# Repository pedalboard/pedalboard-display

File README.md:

# Pedalboard Display

LED ring and OLED display PCB for the [Open Pedalboard](https://github.com/pedalboard) system.

**[Documentation →](https://pedalboard.github.io/pedalboard-display/latest/)**

## Features

- 8 cascaded RGB LED rings (12 individually addressable LEDs each)
- Single serial line addressing (Stemma 3-pin JST-PH)
- 2 additional single LEDs
- 2 ports for 4-wire OLED displays (Stemma 4-pin connectors)

## Links

- [Interactive schematic & PCB viewer](https://pedalboard.github.io/pedalboard-display/latest/board/)
- [DigiKey shared list](https://www.digikey.ch/en/mylists/list/VCPAA9117V)
- Foot switch actuator: [Data Sheet](https://www.cliffuk.co.uk/products/switches/FC7125.pdf) / [3D Model](https://github.com/pedalboard/pedalboard-case/blob/main/generated/actuator.stl)

## License

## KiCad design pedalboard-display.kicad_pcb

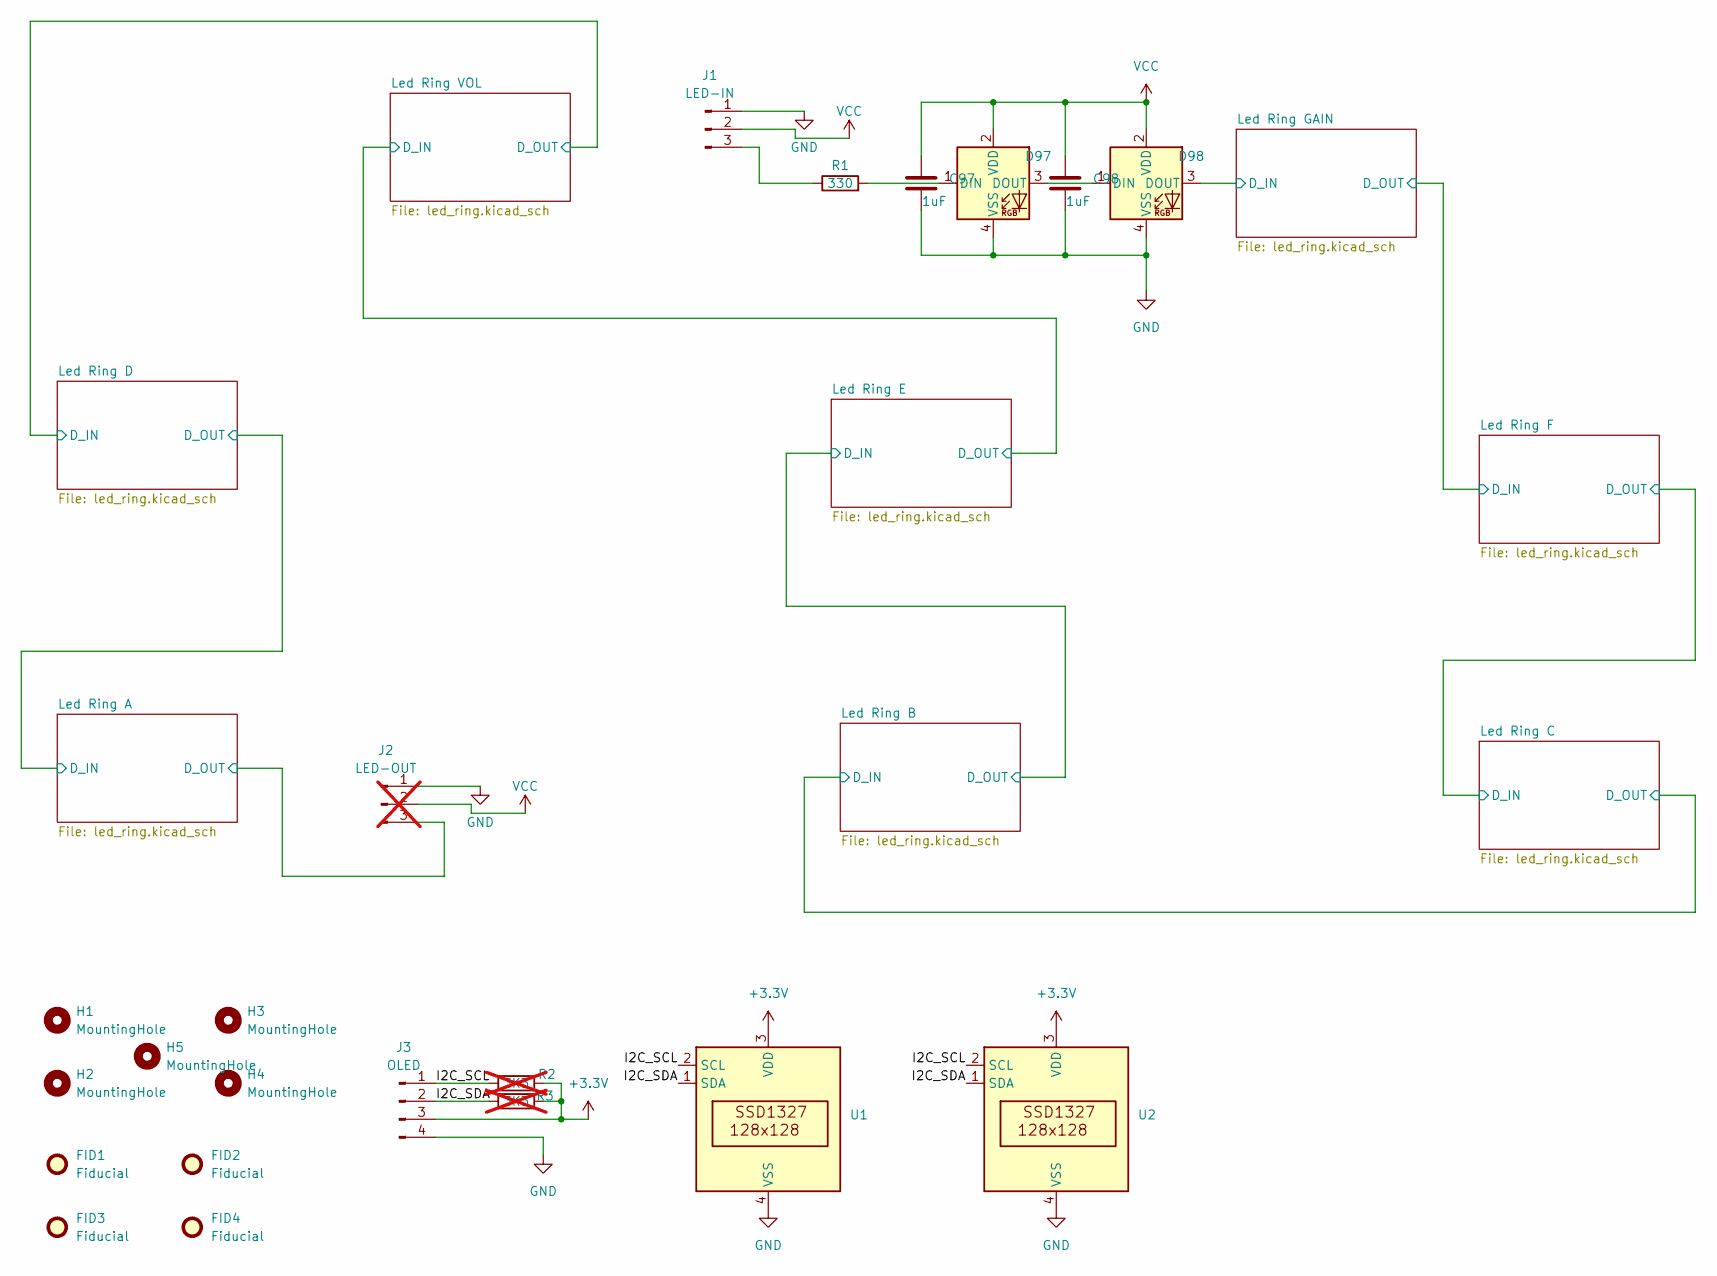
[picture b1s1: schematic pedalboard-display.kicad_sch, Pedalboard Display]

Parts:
C97, C98: 1uF; C_0402_1005Metric
D97, D98: SK6812_EC15; LED_SK6812_EC15_1.5x1.5mm
FID1, FID2, FID3, FID4: Fiducial; Fiducial_0.5mm_Mask1mm
H1, H2, H3, H4, H5: MountingHole; MountingHole_2.5mm
J1: LED-IN; JST_PH_B3B-PH-SM4-TB_1x03-1MP_P2.00mm_Vertical
J2: LED-OUT; JST_PH_B3B-PH-SM4-TB_1x03-1MP_P2.00mm_Vertical; not fitted
J3: OLED; JST_PH_B4B-PH-SM4-TB_1x04-1MP_P2.00mm_Vertical
R1: 330; R_0402_1005Metric
R2, R3: 3K3; R_0805_2012Metric; not fitted
U1, U2: OLED_128x128

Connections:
+3.3V: J3.3, R2.1, R3.1, U1.3 (VDD), U2.3 (VDD)
/I2C_SCL: J3.1, R2.2, U1.2 (SCL), U2.2 (SCL)
/I2C_SDA: J3.2, R3.2, U1.1 (SDA), U2.1 (SDA)
/Led Ring A/D_OUT: J2.3; also elsewhere on the board
/Led Ring GAIN/D_IN: D98.3 (DOUT); also elsewhere on the board
GND: C97.2, C98.2, D97.4 (VSS), D98.4 (VSS), J1.1, J2.1, J3.4, U1.4 (VSS), U2.4 (VSS); also elsewhere on the board
unnamed: D97.1 (DIN), R1.2
unnamed: D97.3 (DOUT), D98.1 (DIN)
unnamed: J1.3, R1.1
VCC: C97.1, C98.1, D97.2 (VDD), D98.2 (VDD), J1.2, J2.2; also elsewhere on the board

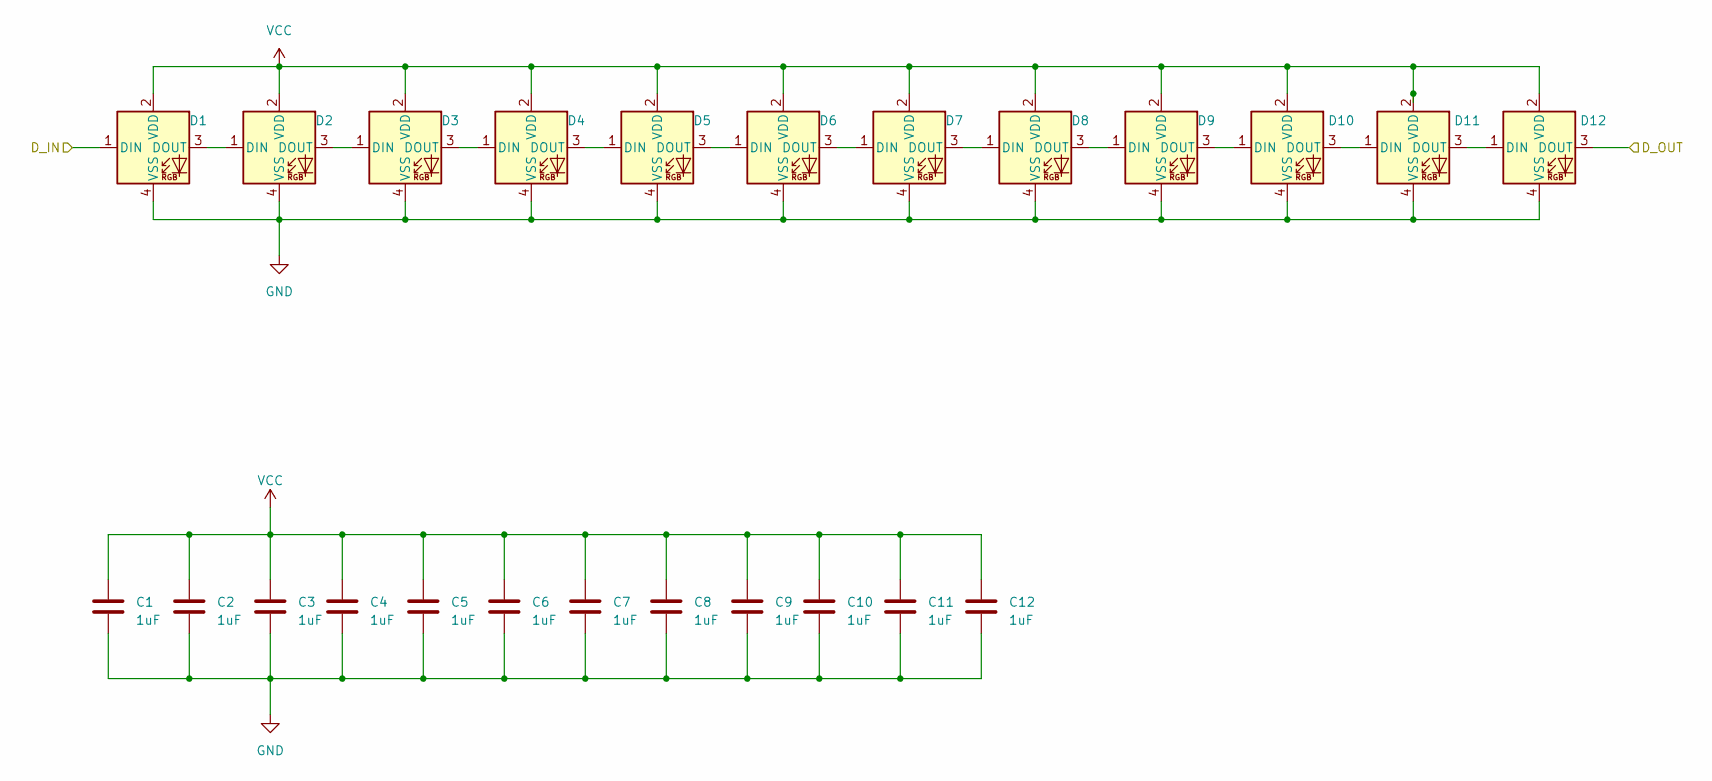
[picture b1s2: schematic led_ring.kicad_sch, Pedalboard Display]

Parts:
C1, C2, C3, C4, C5, C6, C7, C8, C9, C10, C11, C12: 1uF; C_0402_1005Metric
D1, D2, D3, D4, D5, D6, D7, D8, D9, D10, D11, D12: SK6812_EC15; LED_SK6812_EC15_1.5x1.5mm

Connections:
/Led Ring F/D_IN: D12.3 (DOUT); also elsewhere on the board
/Led Ring GAIN/D_IN: D1.1 (DIN); also elsewhere on the board
GND: C1.2, C2.2, C3.2, C4.2, C5.2, C6.2, C7.2, C8.2, C9.2, C10.2, C11.2, C12.2, D1.4 (VSS), D2.4 (VSS), D3.4 (VSS), D4.4 (VSS), D5.4 (VSS), D6.4 (VSS), D7.4 (VSS), D8.4 (VSS), D9.4 (VSS), D10.4 (VSS), D11.4 (VSS), D12.4 (VSS); also elsewhere on the board
unnamed: D1.3 (DOUT), D2.1 (DIN)
unnamed: D2.3 (DOUT), D3.1 (DIN)
unnamed: D3.3 (DOUT), D4.1 (DIN)
unnamed: D4.3 (DOUT), D5.1 (DIN)
unnamed: D5.3 (DOUT), D6.1 (DIN)
unnamed: D6.3 (DOUT), D7.1 (DIN)
unnamed: D7.3 (DOUT), D8.1 (DIN)
unnamed: D8.3 (DOUT), D9.1 (DIN)
unnamed: D9.3 (DOUT), D10.1 (DIN)
unnamed: D10.3 (DOUT), D11.1 (DIN)
unnamed: D11.3 (DOUT), D12.1 (DIN)
VCC: C1.1, C2.1, C3.1, C4.1, C5.1, C6.1, C7.1, C8.1, C9.1, C10.1, C11.1, C12.1, D1.2 (VDD), D2.2 (VDD), D3.2 (VDD), D4.2 (VDD), D5.2 (VDD), D6.2 (VDD), D7.2 (VDD), D8.2 (VDD), D9.2 (VDD), D10.2 (VDD), D11.2 (VDD), D12.2 (VDD); also elsewhere on the board

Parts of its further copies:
C13, C14, C15, C16, C17, C18, C19, C20, C21, C22, C23, C24, C25, C26, C27, C28, C29, C30, C31, C32, C33, C34, C35, C36, C37, C38, C39, C40, C41, C42, C43, C44, C45, C46, C47, C48, C49, C50, C51, C52, C53, C54, C55, C56, C57, C58, C59, C60, C61, C62, C63, C64, C65, C66, C67, C68, C69, C70, C71, C72, C73, C74, C75, C76, C77, C78, C79, C80, C81, C82, C83, C84, C85, C86, C87, C88, C89, C90, C91, C92, C93, C94, C95, C96: 1uF; C_0402_1005Metric
D13, D14, D15, D16, D17, D18, D19, D20, D21, D22, D23, D24, D25, D26, D27, D28, D29, D30, D31, D32, D33, D34, D35, D36, D37, D38, D39, D40, D41, D42, D43, D44, D45, D46, D47, D48, D49, D50, D51, D52, D53, D54, D55, D56, D57, D58, D59, D60, D61, D62, D63, D64, D65, D66, D67, D68, D69, D70, D71, D72, D73, D74, D75, D76, D77, D78, D79, D80, D81, D82, D83, D84, D85, D86, D87, D88, D89, D90, D91, D92, D93, D94, D95, D96: SK6812_EC15; LED_SK6812_EC15_1.5x1.5mm

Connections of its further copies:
/Led Ring A/D_IN: D84.3 (DOUT), D85.1 (DIN)
/Led Ring A/D_OUT: D96.3 (DOUT); also elsewhere on the board
/Led Ring B/D_IN: D36.3 (DOUT), D37.1 (DIN)
/Led Ring B/D_OUT: D48.3 (DOUT), D49.1 (DIN)
/Led Ring C/D_IN: D24.3 (DOUT), D25.1 (DIN)
/Led Ring D/D_IN: D72.3 (DOUT), D73.1 (DIN)
/Led Ring E/D_OUT: D60.3 (DOUT), D61.1 (DIN)
/Led Ring F/D_IN: D13.1 (DIN); also elsewhere on the board
GND: C13.2, C14.2, C15.2, C16.2, C17.2, C18.2, C19.2, C20.2, C21.2, C22.2, C23.2, C24.2, C25.2, C26.2, C27.2, C28.2, C29.2, C30.2, C31.2, C32.2, C33.2, C34.2, C35.2, C36.2, C37.2, C38.2, C39.2, C40.2, C41.2, C42.2, C43.2, C44.2, C45.2, C46.2, C47.2, C48.2, C49.2, C50.2, C51.2, C52.2, C53.2, C54.2, C55.2, C56.2, C57.2, C58.2, C59.2, C60.2, C61.2, C62.2, C63.2, C64.2, C65.2, C66.2, C67.2, C68.2, C69.2, C70.2, C71.2, C72.2, C73.2, C74.2, C75.2, C76.2, C77.2, C78.2, C79.2, C80.2, C81.2, C82.2, C83.2, C84.2, C85.2, C86.2, C87.2, C88.2, C89.2, C90.2, C91.2, C92.2, C93.2, C94.2, C95.2, C96.2, D13.4 (VSS), D14.4 (VSS), D15.4 (VSS), D16.4 (VSS), D17.4 (VSS), D18.4 (VSS), D19.4 (VSS), D20.4 (VSS), D21.4 (VSS), D22.4 (VSS), D23.4 (VSS), D24.4 (VSS), D25.4 (VSS), D26.4 (VSS), D27.4 (VSS), D28.4 (VSS), D29.4 (VSS), D30.4 (VSS), D31.4 (VSS), D32.4 (VSS), D33.4 (VSS), D34.4 (VSS), D35.4 (VSS), D36.4 (VSS), D37.4 (VSS), D38.4 (VSS), D39.4 (VSS), D40.4 (VSS), D41.4 (VSS), D42.4 (VSS), D43.4 (VSS), D44.4 (VSS), D45.4 (VSS), D46.4 (VSS), D47.4 (VSS), D48.4 (VSS), D49.4 (VSS), D50.4 (VSS), D51.4 (VSS), D52.4 (VSS), D53.4 (VSS), D54.4 (VSS), D55.4 (VSS), D56.4 (VSS), D57.4 (VSS), D58.4 (VSS), D59.4 (VSS), D60.4 (VSS), D61.4 (VSS), D62.4 (VSS), D63.4 (VSS), D64.4 (VSS), D65.4 (VSS), D66.4 (VSS), D67.4 (VSS), D68.4 (VSS), D69.4 (VSS), D70.4 (VSS), D71.4 (VSS), D72.4 (VSS), D73.4 (VSS), D74.4 (VSS), D75.4 (VSS), D76.4 (VSS), D77.4 (VSS), D78.4 (VSS), D79.4 (VSS), D80.4 (VSS), D81.4 (VSS), D82.4 (VSS), D83.4 (VSS), D84.4 (VSS), D85.4 (VSS), D86.4 (VSS), D87.4 (VSS), D88.4 (VSS), D89.4 (VSS), D90.4 (VSS), D91.4 (VSS), D92.4 (VSS), D93.4 (VSS), D94.4 (VSS), D95.4 (VSS), D96.4 (VSS); also elsewhere on the board
unnamed: D13.3 (DOUT), D14.1 (DIN)
unnamed: D14.3 (DOUT), D15.1 (DIN)
unnamed: D15.3 (DOUT), D16.1 (DIN)
unnamed: D16.3 (DOUT), D17.1 (DIN)
unnamed: D17.3 (DOUT), D18.1 (DIN)
unnamed: D18.3 (DOUT), D19.1 (DIN)
unnamed: D19.3 (DOUT), D20.1 (DIN)
unnamed: D20.3 (DOUT), D21.1 (DIN)
unnamed: D21.3 (DOUT), D22.1 (DIN)
unnamed: D22.3 (DOUT), D23.1 (DIN)
unnamed: D23.3 (DOUT), D24.1 (DIN)
unnamed: D25.3 (DOUT), D26.1 (DIN)
unnamed: D26.3 (DOUT), D27.1 (DIN)
unnamed: D27.3 (DOUT), D28.1 (DIN)
unnamed: D28.3 (DOUT), D29.1 (DIN)
unnamed: D29.3 (DOUT), D30.1 (DIN)
unnamed: D30.3 (DOUT), D31.1 (DIN)
unnamed: D31.3 (DOUT), D32.1 (DIN)
unnamed: D32.3 (DOUT), D33.1 (DIN)
unnamed: D33.3 (DOUT), D34.1 (DIN)
unnamed: D34.3 (DOUT), D35.1 (DIN)
unnamed: D35.3 (DOUT), D36.1 (DIN)
unnamed: D37.3 (DOUT), D38.1 (DIN)
unnamed: D38.3 (DOUT), D39.1 (DIN)
unnamed: D39.3 (DOUT), D40.1 (DIN)
unnamed: D40.3 (DOUT), D41.1 (DIN)
unnamed: D41.3 (DOUT), D42.1 (DIN)
unnamed: D42.3 (DOUT), D43.1 (DIN)
unnamed: D43.3 (DOUT), D44.1 (DIN)
unnamed: D44.3 (DOUT), D45.1 (DIN)
unnamed: D45.3 (DOUT), D46.1 (DIN)
unnamed: D46.3 (DOUT), D47.1 (DIN)
unnamed: D47.3 (DOUT), D48.1 (DIN)
unnamed: D49.3 (DOUT), D50.1 (DIN)
unnamed: D50.3 (DOUT), D51.1 (DIN)
unnamed: D51.3 (DOUT), D52.1 (DIN)
unnamed: D52.3 (DOUT), D53.1 (DIN)
unnamed: D53.3 (DOUT), D54.1 (DIN)
unnamed: D54.3 (DOUT), D55.1 (DIN)
unnamed: D55.3 (DOUT), D56.1 (DIN)
unnamed: D56.3 (DOUT), D57.1 (DIN)
unnamed: D57.3 (DOUT), D58.1 (DIN)
unnamed: D58.3 (DOUT), D59.1 (DIN)
unnamed: D59.3 (DOUT), D60.1 (DIN)
unnamed: D61.3 (DOUT), D62.1 (DIN)
unnamed: D62.3 (DOUT), D63.1 (DIN)
unnamed: D63.3 (DOUT), D64.1 (DIN)
unnamed: D64.3 (DOUT), D65.1 (DIN)
unnamed: D65.3 (DOUT), D66.1 (DIN)
unnamed: D66.3 (DOUT), D67.1 (DIN)
unnamed: D67.3 (DOUT), D68.1 (DIN)
unnamed: D68.3 (DOUT), D69.1 (DIN)
unnamed: D69.3 (DOUT), D70.1 (DIN)
unnamed: D70.3 (DOUT), D71.1 (DIN)
unnamed: D71.3 (DOUT), D72.1 (DIN)
unnamed: D73.3 (DOUT), D74.1 (DIN)
unnamed: D74.3 (DOUT), D75.1 (DIN)
unnamed: D75.3 (DOUT), D76.1 (DIN)
unnamed: D76.3 (DOUT), D77.1 (DIN)
unnamed: D77.3 (DOUT), D78.1 (DIN)
unnamed: D78.3 (DOUT), D79.1 (DIN)
unnamed: D79.3 (DOUT), D80.1 (DIN)
unnamed: D80.3 (DOUT), D81.1 (DIN)
unnamed: D81.3 (DOUT), D82.1 (DIN)
unnamed: D82.3 (DOUT), D83.1 (DIN)
unnamed: D83.3 (DOUT), D84.1 (DIN)
unnamed: D85.3 (DOUT), D86.1 (DIN)
unnamed: D86.3 (DOUT), D87.1 (DIN)
unnamed: D87.3 (DOUT), D88.1 (DIN)
unnamed: D88.3 (DOUT), D89.1 (DIN)
unnamed: D89.3 (DOUT), D90.1 (DIN)
unnamed: D90.3 (DOUT), D91.1 (DIN)
unnamed: D91.3 (DOUT), D92.1 (DIN)
unnamed: D92.3 (DOUT), D93.1 (DIN)
unnamed: D93.3 (DOUT), D94.1 (DIN)
unnamed: D94.3 (DOUT), D95.1 (DIN)
unnamed: D95.3 (DOUT), D96.1 (DIN)
VCC: C13.1, C14.1, C15.1, C16.1, C17.1, C18.1, C19.1, C20.1, C21.1, C22.1, C23.1, C24.1, C25.1, C26.1, C27.1, C28.1, C29.1, C30.1, C31.1, C32.1, C33.1, C34.1, C35.1, C36.1, C37.1, C38.1, C39.1, C40.1, C41.1, C42.1, C43.1, C44.1, C45.1, C46.1, C47.1, C48.1, C49.1, C50.1, C51.1, C52.1, C53.1, C54.1, C55.1, C56.1, C57.1, C58.1, C59.1, C60.1, C61.1, C62.1, C63.1, C64.1, C65.1, C66.1, C67.1, C68.1, C69.1, C70.1, C71.1, C72.1, C73.1, C74.1, C75.1, C76.1, C77.1, C78.1, C79.1, C80.1, C81.1, C82.1, C83.1, C84.1, C85.1, C86.1, C87.1, C88.1, C89.1, C90.1, C91.1, C92.1, C93.1, C94.1, C95.1, C96.1, D13.2 (VDD), D14.2 (VDD), D15.2 (VDD), D16.2 (VDD), D17.2 (VDD), D18.2 (VDD), D19.2 (VDD), D20.2 (VDD), D21.2 (VDD), D22.2 (VDD), D23.2 (VDD), D24.2 (VDD), D25.2 (VDD), D26.2 (VDD), D27.2 (VDD), D28.2 (VDD), D29.2 (VDD), D30.2 (VDD), D31.2 (VDD), D32.2 (VDD), D33.2 (VDD), D34.2 (VDD), D35.2 (VDD), D36.2 (VDD), D37.2 (VDD), D38.2 (VDD), D39.2 (VDD), D40.2 (VDD), D41.2 (VDD), D42.2 (VDD), D43.2 (VDD), D44.2 (VDD), D45.2 (VDD), D46.2 (VDD), D47.2 (VDD), D48.2 (VDD), D49.2 (VDD), D50.2 (VDD), D51.2 (VDD), D52.2 (VDD), D53.2 (VDD), D54.2 (VDD), D55.2 (VDD), D56.2 (VDD), D57.2 (VDD), D58.2 (VDD), D59.2 (VDD), D60.2 (VDD), D61.2 (VDD), D62.2 (VDD), D63.2 (VDD), D64.2 (VDD), D65.2 (VDD), D66.2 (VDD), D67.2 (VDD), D68.2 (VDD), D69.2 (VDD), D70.2 (VDD), D71.2 (VDD), D72.2 (VDD), D73.2 (VDD), D74.2 (VDD), D75.2 (VDD), D76.2 (VDD), D77.2 (VDD), D78.2 (VDD), D79.2 (VDD), D80.2 (VDD), D81.2 (VDD), D82.2 (VDD), D83.2 (VDD), D84.2 (VDD), D85.2 (VDD), D86.2 (VDD), D87.2 (VDD), D88.2 (VDD), D89.2 (VDD), D90.2 (VDD), D91.2 (VDD), D92.2 (VDD), D93.2 (VDD), D94.2 (VDD), D95.2 (VDD), D96.2 (VDD); also elsewhere on the board

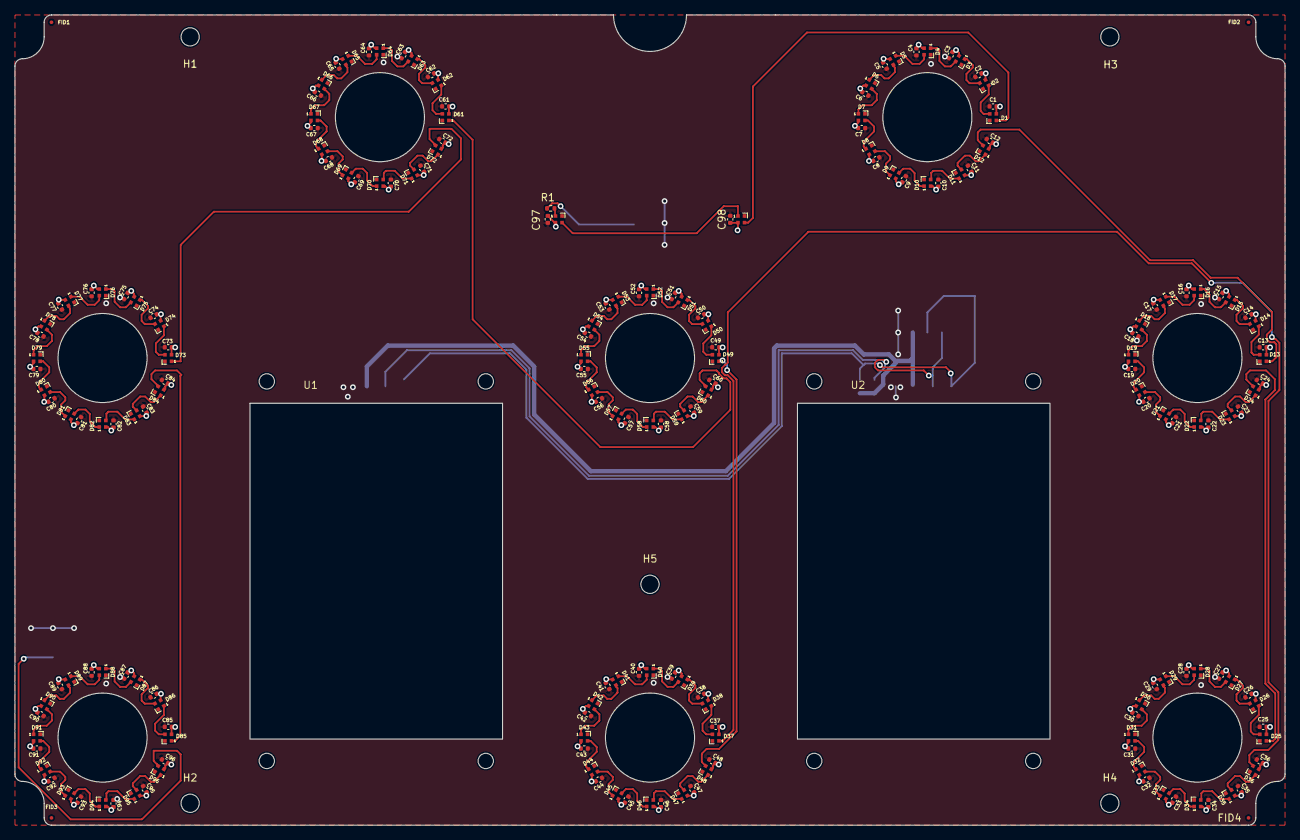
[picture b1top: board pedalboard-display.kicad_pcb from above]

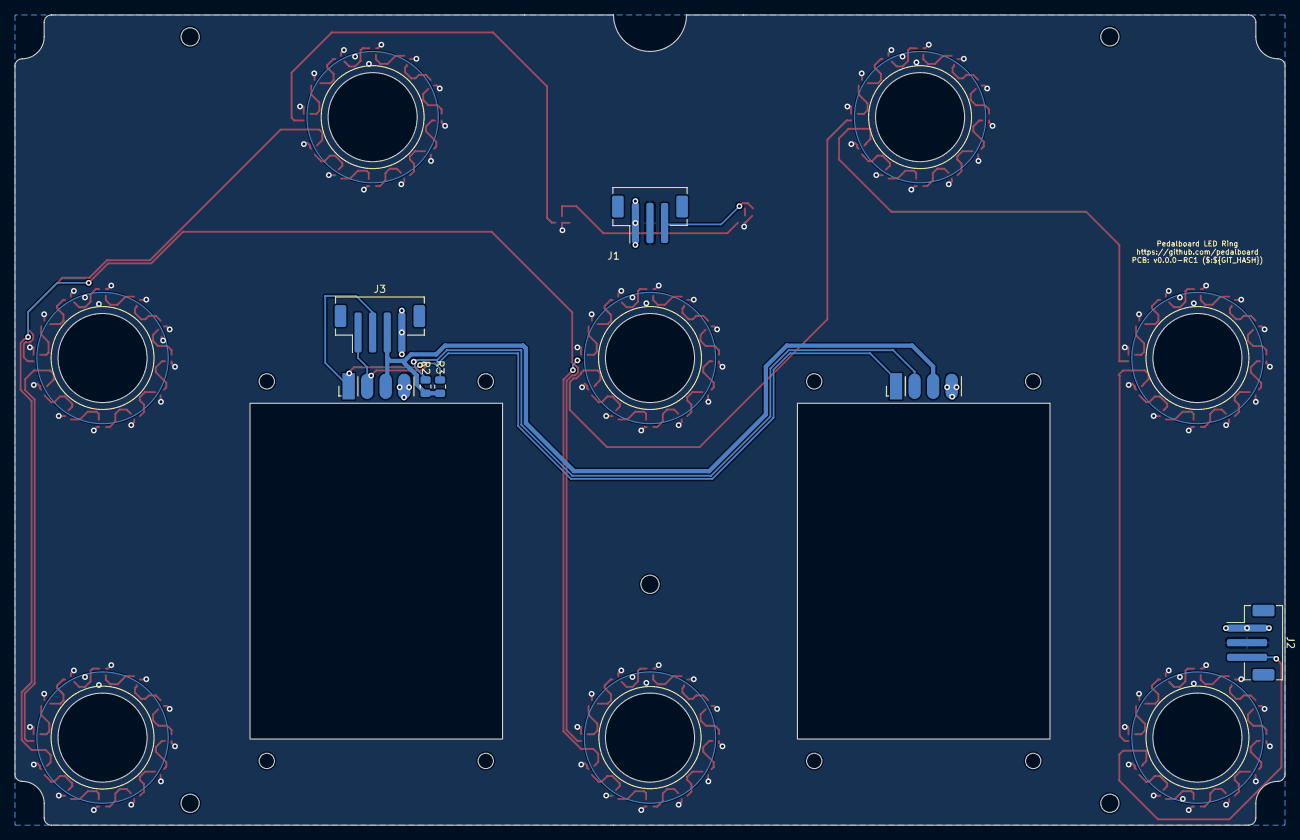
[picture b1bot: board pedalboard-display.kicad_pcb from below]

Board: 2 copper layers, 174.0 x 111.0 mm, 213 parts (5 on the bottom side), 105 nets.

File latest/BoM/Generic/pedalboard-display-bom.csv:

Row,Description,Part,References,Value,Footprint,Quantity Per PCB,Status,Datasheet,Supplier
1,,C,C1 C2 C3 C4 C5 C6 C7 C8 C9 C10 C11 C12 C13 C14 C15 C16 C17 C18 C19 C20 C21 C22 C23 C24 C25 C26 C27 C28 C29 C30 C31 C32 C33 C34 C35 C36 C37 C38 C39 C40 C41 C42 C43 C44 C45 C46 C47 C48 C49 C50 C51 C52 C53 C54 C55 C56 C57 C58 C59 C60 C61 C62 C63 C64 C65 C66 C67 C68 C69 C70 C71 C72 C73 C74 C75 C76 C77 C78 C79 C80 C81 C82 C83 C84 C85 C86 C87 C88 C89 C90 C91 C92 C93 C94 C95 C96 C97 C98,1uF,C_0402_1005Metric,98, ,https://media.digikey.com/pdf/Data%20Sheets/Samsung%20PDFs/C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,https://www.digikey.ch/de/products/detail/samsung-electro-me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
2,,SK6812,D1 D2 D3 D4 D5 D6 D7 D8 D9 D10 D11 D12 D13 D14 D15 D16 D17 D18 D19 D20 D21 D22 D23 D24 D25 D26 D27 D28 D29 D30 D31 D32 D33 D34 D35 D36 D37 D38 D39 D40 D41 D42 D43 D44 D45 D46 D47 D48 D49 D50 D51 D52 D53 D54 D55 D56 D57 D58 D59 D60 D61 D62 D63 D64 D65 D66 D67 D68 D69 D70 D71 D72 D73 D74 D75 D76 D77 D78 D79 D80 D81 D82 D83 D84 D85 D86 D87 D88 D89 D90 D91 D92 D93 D94 D95 D96 D97 D98,SK6812_EC15,LED_SK6812_EC15_1.5x1.5mm,98, ,https://www.inolux-corp.com/datasheet/SMDLED/Addressable%20L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,https://www.digikey.ch/en/products/detail/inolux/IN-PI15TAT5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
3,,Conn_01x03_Pin,J1,JST PH 3,JST_PH_B3B-PH-SM4-TB_1x03-1MP_P2.00mm_Vertical,1, ,https://www.jst-mfg.com/product/pdf/eng/ePH.pdf,https://www.digikey.ch/de/products/detail/jst-sales-america-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
4,"Generic connector, single row, 01x04, script generated",Conn_01x04_Pin,J3,JST PH 4,JST_PH_B4B-PH-SM4-TB_1x04-1MP_P2.00mm_Vertical,1, ,https://www.jst-mfg.com/product/pdf/eng/ePH.pdf,https://www.digikey.ch/de/products/detail/jst-sales-america-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
5,,R,R1,330,R_0402_1005Metric,1, ,https://www.passivecomponent.com/wp-content/uploads/chipR/AS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,https://www.digikey.ch/en/products/detail/walsin-technology-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
6,,OLED,U1 U2,OLED I2C,OLED_128x128,2, ,img/GME12812.pdf,https://www.aliexpress.com/item/1005005253671396.html





Project info:
Schematic:,pedalboard-display
Variant:,default
Revision:,1.0.1-RC
Date:,2024-10-16
KiCad Version:,9.0.7+1
Statistics:
Component Groups:,8
Component Count:,204 (202 SMD/ 2 THT)
Fitted Components:,201 (199 SMD/ 2 THT)
Number of PCBs:,1
Total Components:,201

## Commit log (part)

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2024-01-10 Rename files
2024-01-10 Remove pnp job (better start from scratch)
2024-01-10 Replace name in file contents
2024-01-10 Bump version down
2024-01-10 Fix README.md
2024-01-10 Fix pipeline
2024-01-10 Extend Schema to 8 LED rings
2024-01-10 Fix diff version
2024-01-10 First placement of parts on PCB
2024-02-04 Connectedx all LEDs
2024-02-04 Improve user drawings
2024-02-04 Fix deployment variable
2024-02-04 Place fiducials
2024-10-04 Update versions
2024-10-04 Fix ground connections
2024-10-04 Fix DRC errors
2024-10-04 Improve jig size
2024-10-04 Upgrade checkout action
2024-10-04 Fix title
2024-10-04 First OLED idea
2024-10-05 First OLED wiring
2024-10-05 Only use one reset circuit
2024-10-05 Improve page title
2024-10-05 First display module version
2024-10-06 Positions for OLED modules
2024-10-06 Add 3d models for JST connectors
2024-10-06 Connect all
2024-10-06 Small text improvments
2024-10-06 Silkscreen on top
2024-10-06 Fix silkscreen bug
2024-10-06 Improve size of 3d pictures
2024-10-06 Add TODO
2024-10-06 Fix Silkscreen warnings
2024-10-06 Cleanup tracks (move vias to save space
2024-10-06 Cleanup tracks
2024-10-06 Cleanup vias
2024-10-06 Reset 3d views to default
2024-10-06 Remove silkscreen circle
2024-10-06 Add Mounting Holes
2024-10-06 Fix 3d rendering
2024-10-06 Remove TODO
2024-10-07 Move single leds
2024-10-08 Add optional pull up resistors
2024-10-08 TODO added
2024-10-08 Add Logo
2024-10-08 Add Open Hardware Logo
2024-10-08 Fix logo
2024-10-08 Put single leds at the end of the line
2024-10-08 Small cleanups
2024-10-08 Better mounting holes for displays
2024-10-08 Increase fiducial size
2024-10-08 Improve mounting holes for OLED
2024-10-08 Add circle for single led whole on user layer
2024-10-09 Add actuators 3d models
2024-10-09 Add display models
2024-10-09 Add 3d models for displays
2024-10-09 Add TODOs
2024-10-13 Update hole positions
2024-10-14 Use led-ring-encoder-washer
2024-10-15 Fix DRC errors, and clean space for audio connectors
2024-10-15 Enable ERC
2024-10-15 Update symbol from library
2024-10-15 Update GND symbol from library
2024-10-15 Cleanup schematic led out
2024-10-15 Cleanup schematic led in
2024-10-15 Add Makefile
2024-10-15 Use ascii format
2024-10-15 Help was missing
2024-10-16 Bump version to 1.0.0
2024-10-16 Bump version to 1.0.1-RC
2024-10-16 Add 3D views
2024-10-17 Improve BOM
2024-10-17 Change LEDs in bom
2024-10-17 Improve BOM (JST)
2024-10-17 Revert README to latest
2024-10-17 Improve Makefile (custom bom)
2024-10-17 Add link to digikey list
2024-10-27 First import of pnp files
2024-10-30 Add bom2inventree script
2024-10-30 change bom converter file name
2024-11-03 Set the board location for pnp
2024-11-03 Disable all pacments by default
2024-11-03 Reset placed parts
2024-11-06 Improve the Stencil Jig size
2024-12-15 Update jig size
2024-12-15 Use short git hash in Makefile
2024-12-16 Replace deprecated parameter
2024-12-24 Add I2C addresses of the displays
2024-12-24 Fix text
2025-04-21 Update to kicad 9
2025-04-21 Changelog
2026-04-14 Deploy to gh-pages branch with version picker
    - Replace cross-repo deploy with gh-pages in same repo
    - Add version picker landing page
    - Tag-triggered versioned deploy
    - Update README URLs
2026-04-14 Initial gh-pages commit
2026-04-14 Deploying to gh-pages from @ pedalboard/pedalboard-display@3a921628f1b1ea8ff82f12ce4ba55bb07f8b0647 🚀
2026-04-14 Fix GitHub repo link
2026-04-14 Deploying to gh-pages from @ pedalboard/pedalboard-display@c637ea6a6f594176a6ef45805cfda6feb399981b 🚀
2026-04-18 reset versions.json for new theme
2026-04-18 switch to hugo-kicad-site theme
2026-04-18 update README: link to Hugo doc site
2026-04-18 Deploying to gh-pages from @ pedalboard/pedalboard-display@9dde7ddff6c68ce820a8b35a80bac42cd7ae5fcf 🚀
2026-04-18 add v1.0.0 link to old site
2026-04-18 add OSHWA CH000019 badge
2026-04-18 overview: add OSHWA and license badges
2026-04-18 Deploying to gh-pages from @ pedalboard/pedalboard-display@09480a15819c00b2e829cfb5fd35e7f757412bc9 🚀
2026-04-18 remove redundant badges from overview (now in footer)
2026-04-18 Deploying to gh-pages from @ pedalboard/pedalboard-display@7c89816945d76d890c784b004e1085228ecb8a92 🚀
2026-04-18 Deploying to gh-pages from @ pedalboard/pedalboard-display@eb0dc56af4e1ac4fbc7fcac972920c60ccf994d0 🚀
2026-04-18 overview: cross-link related boards
2026-04-18 README: add OSHWA badge, consistent structure
2026-04-18 Deploying to gh-pages from @ pedalboard/pedalboard-display@33b705267c5306b56a23c8c97eda0776f9839a25 🚀
2026-04-21 site: add .mise.toml, update theme vendor (hugo-kicad-site v1.0.3)
2026-04-21 ci: switch to KiCad 10 container with kicad-packages3d
2026-04-21 ci: remove kibot_install (3D models now cached by workflow)
2026-04-21 Deploying to gh-pages from @ pedalboard/pedalboard-display@5b95d989cab1302c6f05e4155edb81e8fd4337d0 🚀
2026-04-22 migrate to KiCad 10 file format
2026-04-22 disable download_datasheets due to KiBot bug INTI-CMNB/KiBot#919
2026-04-22 fix R1 datasheet URL (broken SSL on passivecomponent.com), re-enable download_datasheets
2026-04-22 align blender 3D renders with template (two perspectives, render only)
2026-04-22 KiCad 10 CI cleanup: remove HPGL/pcbdraw/render_3d outputs, add text variables, use workflow defaults
2026-04-22 Disable download_datasheets (SSL failures on external sites)
2026-04-22 Deploying to gh-pages from @ pedalboard/pedalboard-display@557fe1e7ba489c80f5472a749895be0239d2892c 🚀
2026-04-22 Increase Blender render resolution to 4K (3840x2160)
2026-04-22 Reduce Blender render resolution to QHD (2560x1440)
2026-04-22 Deploying to gh-pages from @ pedalboard/pedalboard-display@a1591e675c92a22acb410d606cac5123d2ddc3d8 🚀
2026-04-22 Update hugo-kicad-site theme to latest main
2026-04-22 Deploying to gh-pages from @ pedalboard/pedalboard-display@47610d8a04280b42de2dbbcfe925e15f80518237 🚀
2026-04-22 Deploying to gh-pages from @ pedalboard/pedalboard-display@1dea77040afab2475d6b5a99b8619bfc616832cb 🚀
2026-04-23 Add GitHub icon to header menu link
2026-04-23 Deploying to gh-pages from @ pedalboard/pedalboard-display@94b9aaab46dadc32d90fb2ce87e07c12230266f2 🚀
2026-05-06 Migrate site theme to Hextra (v1.1.0)
2026-05-06 Deploying to gh-pages from @ pedalboard/pedalboard-display@438f7e58734b3b020945bb90820d26714e298b30 🚀
2026-05-12 Deploying to gh-pages from @ pedalboard/pedalboard-display@d3610b5c8bf776cfd01596e6e69ede285f548dad 🚀
2026-05-13 Remove _vendor directory (use Hugo module resolution)
2026-05-13 Deploying to gh-pages from @ pedalboard/pedalboard-display@433e9090f67a40721300e903c0206a3a29c8822a 🚀

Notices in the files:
README.md:
[OSHWA Certified](https://certification.oshwa.org/ch000019.html) [License: CERN-OHL-P-2.0](LICENSE.txt)
latest/kicad/led_ring.kicad_sch:
License: CERN Open Hardware Licence Version 2 - Permissive
